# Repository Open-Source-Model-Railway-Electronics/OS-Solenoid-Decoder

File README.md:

# OS-Solenoid-Decoder

The OS-Solenoid-Decoder is a simple, powerful DCC accessory decoder for switching:

• Turnouts (point motors),  
• Relays,  
• Uncouplers,  
• And other solenoid-driven devices.  

It can handle loads of up to 5 amps and supports almost any type of point motor.  
It can also be used in combination with OS-relays to handle frog polarisation for electrofrog and unifrog points.  

This decoder is designed to be:

• Easy to wire — with pluggable screw terminals,  
• Easy to configure — using only standard DCC accessory commands,  
• Modular — with optional relay and transistor expansion boards,  
• And robust — with built-in overload protection.  

Whether you're building a large layout or just want something that works without hassle:  
this decoder is made to get the job done, without needing a degree in electronics.

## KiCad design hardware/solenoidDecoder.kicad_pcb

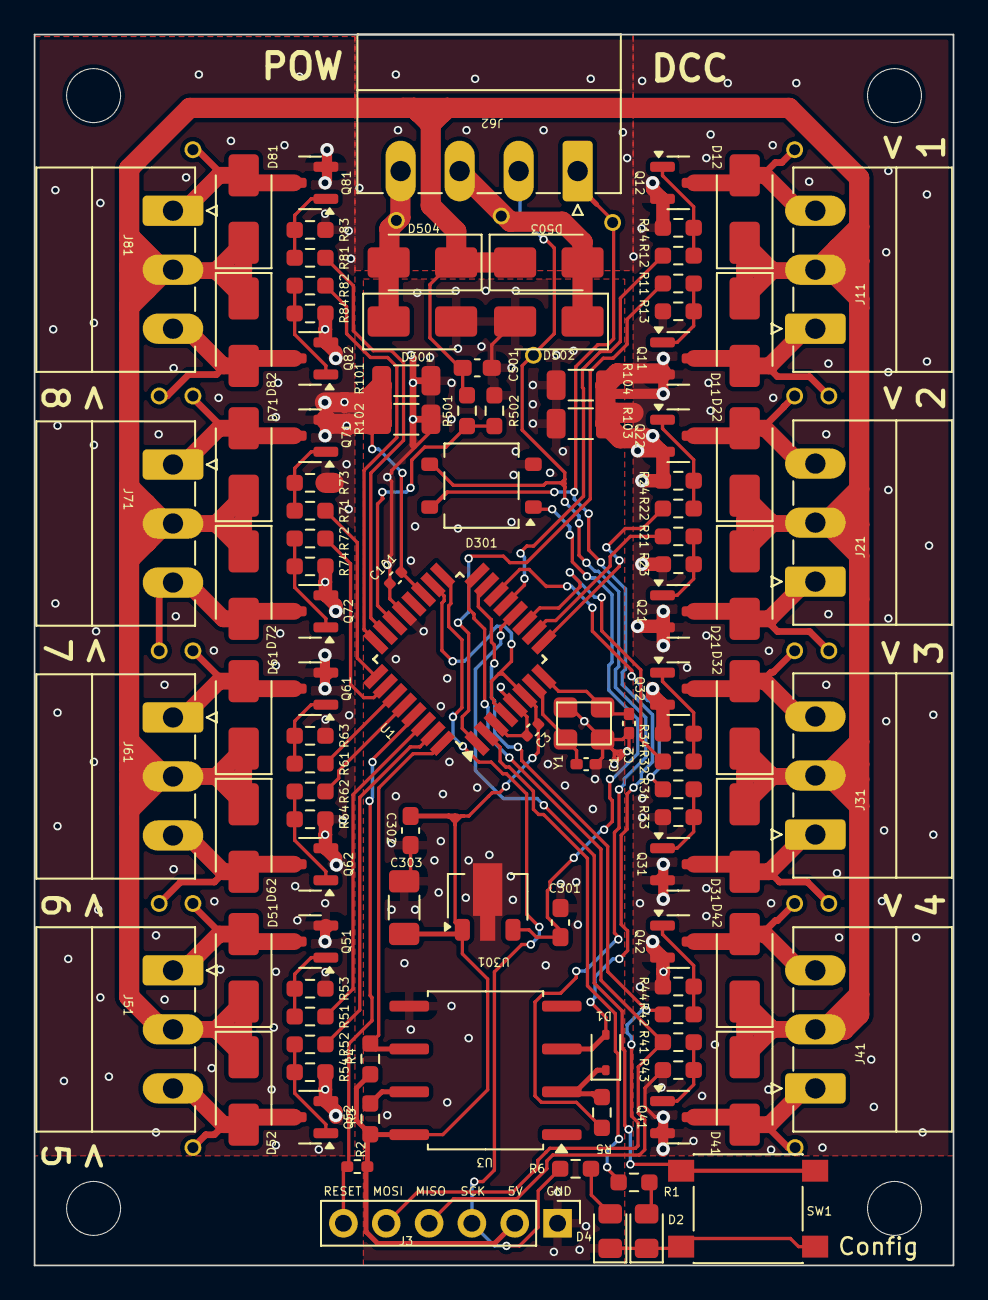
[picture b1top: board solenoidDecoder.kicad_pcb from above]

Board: 2 copper layers, 54.5 x 73.0 mm, 127 parts (0 on the bottom side), 69 nets.

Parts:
C1, C2: 12pF; C_0402_1005Metric_Pad0.74x0.62mm_HandSolder
C3, C101: 100nF; C_0402_1005Metric
C301: 330nF; C_0603_1608Metric_Pad1.08x0.95mm_HandSolder
C302, C501: 100nF; C_0603_1608Metric_Pad1.08x0.95mm_HandSolder
C303: 100uF; C_1206_3216Metric_Pad1.33x1.80mm_HandSolder
D1: D; D_SOD-323
D2, D4: LED; LED_0805_2012Metric_Pad1.15x1.40mm_HandSolder
D11, D21, D31, D41, D51, D61, D71, D81: SS34; D_SMA
D12, D22, D32, D42, D52, D62, D72, D82: D_SMA
D301: MB10S; TO-269AA
D501, D502, D503, D504: SS53; D_SMA
J3: ICSP; PinHeader_1x06_P2.54mm_Vertical
J11, J21, J31, J41, J51, J61, J71, J81: PhoenixContact_MC_1,5_3-G-3.5_1x03_P3.50mm_Horizontal
J62: Screw_Terminal_01x04; PhoenixContact_MC_1,5_4-G-3.5_1x04_P3.50mm_Horizontal
Q11, Q12, Q21, Q22, Q31, Q32, Q41, Q42, Q51, Q52, Q61, Q62, Q71, Q72, Q81, Q82: AO3400A; SOT-23
R1, R3, R4, R502: 10k; R_0603_smalltext
R2: 10k; R_0402_1005Metric_Pad0.72x0.64mm_HandSolder
R5: 1k5; R_0603_smalltext
R6: 6k2; R_0603_1608Metric_Pad0.98x0.95mm_HandSolder
R11, R12, R21, R22, R31, R32, R41, R42, R51, R52, R61, R62, R71, R72, R81, R82: 22R; R_0603_1608Metric_Pad0.98x0.95mm_HandSolder
R13, R14, R23, R24, R33, R34, R43, R44, R53, R54, R63, R64, R73, R74, R83, R84: 10k; R_0603_1608Metric_Pad0.98x0.95mm_HandSolder
R101, R102, R103, R104: 0R1; R_1206_3216Metric
R501: 47k; R_0603_smalltext
SW1: SW_SPST; tactile_SMD_6mm
TP1, TP2, TP3, TP4, TP5, TP6, TP7, TP8, TP9, TP10, TP11, TP12, TP13, TP14, TP15, TP16, TP17, TP18, TP19, TP20: TestPoint; pogoTestPad
U1: ATmega328-A; TQFP-32_7x7mm_P0.8mm
U3: 6N137; SOP-8_6.62x9.15mm_P2.54mm
U301: L78L05_SOT89; SOT-89-3
Y1: Crystal_GND2; crystal_arduino

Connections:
+5V: C3.1, C302.1, C303.1, J3.2, R2.1, R3.1, R4.1, U1.4 (VCC), U1.6 (VCC), U1.18 (AVCC), U3.8 (VCC), U301.1 (OUT)
/DCC/A: D1.2 (A), D301.4, J62.1, TP17.1, U3.3 (C)
/DCC/B: D301.3, J62.2, R5.1, TP18.1
/DCC/DCC_TTL: R4.2, U1.32 (PD2), U3.6 (VO)
/POWER/A: D501.1 (K), D504.2 (A), J62.4, TP19.1
/POWER/B: D502.1 (K), D503.2 (A), J62.3, TP20.1
/POWER/coilVoltage: R501.2, R502.1, U1.22 (ADC7)
/mosfets1/A: R12.1, U1.13 (PB1)
/mosfets1/B: R11.1, U1.1 (PD3)
/mosfets2/A: R22.1, U1.9 (PD5)
/mosfets2/B: R21.1, U1.10 (PD6)
/mosfets3/A: R32.1, U1.11 (PD7)
/mosfets3/B: R31.1, U1.14 (PB2)
/mosfets4/A: J3.5, R42.1, U1.15 (PB3)
/mosfets4/B: J3.4, R41.1, U1.16 (PB4)
/mosfets5/A: R52.1, U1.31 (PD1)
/mosfets5/B: R51.1, U1.30 (PD0)
/mosfets6/A: R62.1, U1.28 (PC5)
/mosfets6/B: R61.1, U1.27 (PC4)
/mosfets7/A: R72.1, U1.26 (PC3)
/mosfets7/B: R71.1, U1.25 (PC2)
/mosfets8/A: R82.1, U1.24 (PC1)
/mosfets8/B: R81.1, U1.23 (PC0)
/uController/LED: J3.3, R6.1, U1.17 (PB5)
/uController/LED_BLUE: R1.1, U1.2 (PD4)
/uController/RESET: J3.6, R2.2, U1.29 (~RESET/PC6)
/uController/X1: C1.2, U1.7 (XTAL1/PB6), Y1.1
/uController/X2: C2.2, U1.8 (XTAL2/PB7), Y1.3
GND: C1.1, C2.1, C3.2, C101.2, C301.2, C302.2, C303.2, C501.2, D2.1 (K), D4.1 (K), D301.2 (-), D501.2 (A), D502.2 (A), J3.1, R101.2, R102.2, R103.2, R104.2, R502.2, SW1.2 (B), U1.3 (GND), U1.5 (GND), U1.21 (GND), U3.5 (GND), U301.2 (GND), Y1.2 (GND), Y1.4 (GND)
GND_COIL: C101.1, Q11.2 (S), Q12.2 (S), Q21.2 (S), Q22.2 (S), Q31.2 (S), Q32.2 (S), Q41.2 (S), Q42.2 (S), Q51.2 (S), Q52.2 (S), Q61.2 (S), Q62.2 (S), Q71.2 (S), Q72.2 (S), Q81.2 (S), Q82.2 (S), R13.1, R14.1, R23.1, R24.1, R33.1, R34.1, R43.1, R44.1, R53.1, R54.1, R63.1, R64.1, R73.1, R74.1, R83.1, R84.1, R101.1, R102.1, R103.1, R104.1, U1.19 (ADC6)
unnamed: D1.1 (K), R5.2, U3.2 (A)
unnamed: D2.2 (A), R1.2
unnamed: D4.2 (A), R6.2
unnamed: D11.2 (A), J11.1, Q11.3 (D), TP3.1
unnamed: D12.2 (A), J11.3, Q12.3 (D), TP4.1
unnamed: D21.2 (A), J21.1, Q21.3 (D), TP1.1
unnamed: D22.2 (A), J21.3, Q22.3 (D), TP2.1
unnamed: D31.2 (A), J31.1, Q31.3 (D), TP5.1
unnamed: D32.2 (A), J31.3, Q32.3 (D), TP6.1
unnamed: D41.2 (A), J41.1, Q41.3 (D), TP7.1
unnamed: D42.2 (A), J41.3, Q42.3 (D), TP8.1
unnamed: D51.2 (A), J51.1, Q51.3 (D), TP9.1
unnamed: D52.2 (A), J51.3, Q52.3 (D), TP10.1
unnamed: D61.2 (A), J61.1, Q61.3 (D), TP11.1
unnamed: D62.2 (A), J61.3, Q62.3 (D), TP12.1
unnamed: D71.2 (A), J71.1, Q71.3 (D), TP13.1
unnamed: D72.2 (A), J71.3, Q72.3 (D), TP14.1
unnamed: D81.2 (A), J81.1, Q81.3 (D), TP15.1
unnamed: D82.2 (A), J81.3, Q82.3 (D), TP16.1
unnamed: C301.1, D301.1 (+), U301.3 (IN)
unnamed: Q11.1 (G), R11.2, R13.2
unnamed: Q12.1 (G), R12.2, R14.2
unnamed: Q21.1 (G), R21.2, R23.2
unnamed: Q22.1 (G), R22.2, R24.2
unnamed: Q31.1 (G), R31.2, R33.2
unnamed: Q32.1 (G), R32.2, R34.2
unnamed: Q41.1 (G), R41.2, R43.2
unnamed: Q42.1 (G), R42.2, R44.2
unnamed: Q51.1 (G), R51.2, R53.2
unnamed: Q52.1 (G), R52.2, R54.2
unnamed: Q61.1 (G), R61.2, R63.2
unnamed: Q62.1 (G), R62.2, R64.2
unnamed: Q71.1 (G), R71.2, R73.2
unnamed: Q72.1 (G), R72.2, R74.2
unnamed: Q81.1 (G), R81.2, R83.2
unnamed: Q82.1 (G), R82.2, R84.2
unnamed: SW1.1 (A), U1.12 (PB0)
unnamed: R3.2, U3.7 (EN)
VCC: C501.1, D11.1 (K), D12.1 (K), D21.1 (K), D22.1 (K), D31.1 (K), D32.1 (K), D41.1 (K), D42.1 (K), D51.1 (K), D52.1 (K), D61.1 (K), D62.1 (K), D71.1 (K), D72.1 (K), D81.1 (K), D82.1 (K), D503.1 (K), D504.1 (K), J11.2, J21.2, J31.2, J41.2, J51.2, J61.2, J71.2, J81.2, R501.1

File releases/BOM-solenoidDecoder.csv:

Comment,Designator,Footprint,LCSC
6N137,U3,SOP-8_6.62x9.15mm_P2.54mm,C110020
Crystal_GND2,Y1,crystal_arduino,C13738
100nF,"C302,C501",C_0603_1608Metric_Pad1.08x0.95mm_HandSolder,C14663
ATmega328-A,U1,TQFP-32_7x7mm_P0.8mm,C14877
100uF,C303,C_1206_3216Metric_Pad1.33x1.80mm_HandSolder,C15008
12pF,"C1,C2",C_0402_1005Metric_Pad0.74x0.62mm_HandSolder,C1547
330nF,C301,C_0603_1608Metric_Pad1.08x0.95mm_HandSolder,C1615
AO3400A,"Q11,Q12,Q21,Q22,Q31,Q32,Q41,Q42,Q51,Q52,Q61,Q62,Q71,Q72,Q81,Q82",SOT-23,C20917
D,D1,D_SOD-323,C2128
1k5,R5,R_0603_smalltext,C22843
22R,"R11,R12,R21,R22,R31,R32,R41,R42,R51,R52,R61,R62,R71,R72,R81,R82",R_0603_1608Metric_Pad0.98x0.95mm_HandSolder,C23345
MB10S,D301,TO-269AA,C2488
0R1,"R101,R102,R103,R104",R_1206_3216Metric,C25334
10k,R2,R_0402_1005Metric_Pad0.72x0.64mm_HandSolder,C25744
10k,"R1,R13,R14,R23,R24,R3,R33,R34,R4,R43,R44,R502,R53,R54,R63,R64,R73,R74,R83,R84",R_0603_smalltext,C25804
47k,R501,R_0603_smalltext,C25819
100nF,"C101,C3",C_0402_1005Metric,C307331
SW_SPST,SW1,tactile_SMD_6mm,C381050
6k2,R6,R_0603_1608Metric_Pad0.98x0.95mm_HandSolder,C4260
L78L05_SOT89,U301,SOT-89-3,C42738
LED,"D2,D4",LED_0805_2012Metric_Pad1.15x1.40mm_HandSolder,C84256
SS34,"D11,D12,D21,D22,D31,D32,D41,D42,D501,D502,D503,D504,D51,D52,D61,D62,D71,D72,D81,D82",D_SMA,C8678
~,"J11,J21,J31,J41,J51,J61,J71,J81","PhoenixContact_MC_1,5_3-G-3.5_1x03_P3.50mm_Horizontal",C880573
Screw_Terminal_01x04,J62,"PhoenixContact_MC_1,5_4-G-3.5_1x04_P3.50mm_Horizontal",C880574

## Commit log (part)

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2025-06-13 Added initial files
2025-06-18 organized board files and added pictures
2025-06-19 Toegevoegd: handleiding (manual.odt)
2025-06-19 Hersteld: handleiding toegevoegd in docs/
2025-06-20 finished 1st draft of the manual
2025-06-20 added flow chart for config menu
2025-06-23 Added manual.pdf and updated readme file
2025-06-23 corrected Manual link in readme
2025-07-18 updated manual with how to wire GP relay extention to be used as frog polaization
2025-10-27 removed obsolete build and upload files
2025-11-07 transformed manual in MD file system
2025-11-11 renamed manual correctly
2025-11-11 updated minor bug in manual
2025-11-15 upadted readme
2026-05-22 Made new logger and simulator tool. Also let Claude AI do some bugsquashing for me.
2026-05-22 Split code into several files
2026-05-24 added translations
2026-05-28 changed tasks.json
